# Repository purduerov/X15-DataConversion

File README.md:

# Readme for X15-DataConversion

Whenever you make a new part, download the datasheet and save it here _**and**_ with the part in the parts library

Always pull other people's changes before beginning to work
`git pull`

Be sure to push your changes after  working on them. Run:
1. `git add .` to add any files in this directory or a subdirectory
or `git add -u` to add any modified files
2. (Optional) `git clean -nX` to see what ignored files can be removed
	`git clean -fX` removes ignored files (Eagle backups)
3. `git commit -m "helpful commit message"` with a description of the work that you did
4. `git push` to push your work to github

Other helpful commands
* `git status` says information about modified and staged files
* `git log` shows the recent commits of the repository
* `git log filename.extension` show the recent commits for just that file
* `git checkout first-couple-letter-of-commit-id` lets you go back to a previous version
* `git checkout master` brings you back to the latest commit
* `git tag` lists the tags
* `git tag -a orderX -m "the version of the board placed for the X'th order"` tag a specific commit
* `git push --tags` needed to push tags to remote
* `git show orderX` show the commit log for the given tag
* `git checkout orderX` go back and interact with the files at the tagged commit

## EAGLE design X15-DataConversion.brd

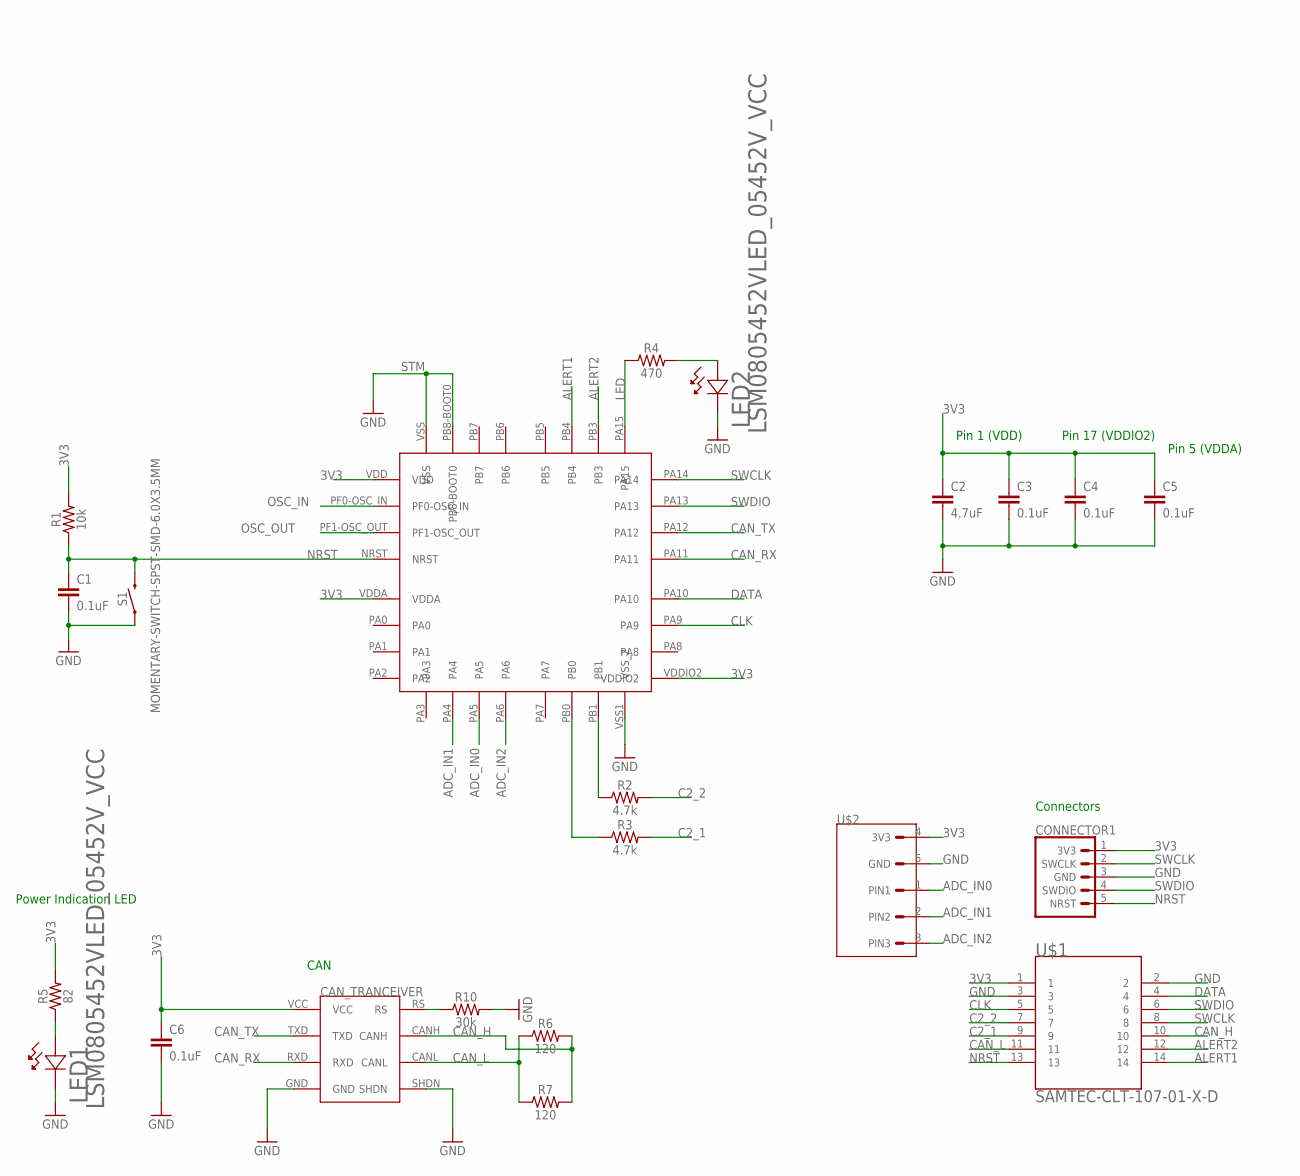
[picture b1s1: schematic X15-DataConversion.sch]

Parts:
C1, C3, C4, C5, C6: 0.1uF; 0603
C2: 4.7uF; 0603
CAN_TRANCEIVER: MAX3058ASA+
CONNECTOR1: 3V3 -SWCLK-GND-SWDIO- NRST; 1X05
LED1, LED2: LSM0805452VLED_05452V_VCC; LED_05452V_VCC
R1: 10k; 0603
R2, R3: 4.7k; 0603
R4: 470; 0603
R5: 82; 0603
R6, R7: 120; 0603
R10: 30k; 0603
S1: MOMENTARY-SWITCH-SPST-SMD-6.0X3.5MM; TACTILE_SWITCH_SMD_6.0X3.5MM
STM: STM32F042K6T6
U$1: BACKPLANE->DATACONV; SAMTEC-CLT-107-01-X-D-BACKPLANE
U$2: STM_CONN; 1X05

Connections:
3V3: C2.1, C3.1, C4.1, C5.1, C6.1, CAN_TRANCEIVER.VCC, CONNECTOR1.1 (3V3), R1.2, R5.2, STM.VDD, STM.VDDA, STM.VDDIO2, U$1.1, U$2.4 (3V3)
ADC_IN0: STM.PA5, U$2.1 (PIN1)
ADC_IN1: STM.PA4, U$2.2 (PIN2)
ADC_IN2: STM.PA6, U$2.3 (PIN3)
ALERT1: STM.PB4, U$1.14
ALERT2: STM.PB3, U$1.12
C2_1: R3.2, U$1.9
C2_2: R2.2, U$1.7
CAN_H: CAN_TRANCEIVER.CANH, R6.2, R7.2, U$1.10
CAN_L: CAN_TRANCEIVER.CANL, R6.1, R7.1, U$1.11
CAN_RX: CAN_TRANCEIVER.RXD, STM.PA11
CAN_TX: CAN_TRANCEIVER.TXD, STM.PA12
CLK: STM.PA9, U$1.5
DATA: STM.PA10, U$1.4
GND: C1.2, C2.2, C3.2, C4.2, C5.2, C6.2, CAN_TRANCEIVER.GND, CAN_TRANCEIVER.SHDN, CONNECTOR1.3 (GND), LED1.2, LED2.2, R10.2, S1.1, STM.PB8-BOOT0, STM.VSS, STM.VSS1 (VSS_2), U$1.2, U$1.3, U$2.5 (GND)
LED: R4.1, STM.PA15
unnamed: LED1.1, R5.1
unnamed: CAN_TRANCEIVER.RS, R10.1
unnamed: R2.1, STM.PB1
unnamed: R3.1, STM.PB0
unnamed: LED2.1, R4.2
NRST: C1.1, CONNECTOR1.5 (NRST), R1.1, S1.2, STM.NRST, U$1.13
OSC_IN: STM.PF0-OSC_IN
OSC_OUT: STM.PF1-OSC_OUT
SWCLK: CONNECTOR1.2 (SWCLK), STM.PA14, U$1.8
SWDIO: CONNECTOR1.4 (SWDIO), STM.PA13, U$1.6

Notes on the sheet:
Power Indication LED
Connectors
CAN
Pin 1 (VDD)
Pin 17 (VDDIO2)
Pin 5 (VDDA)

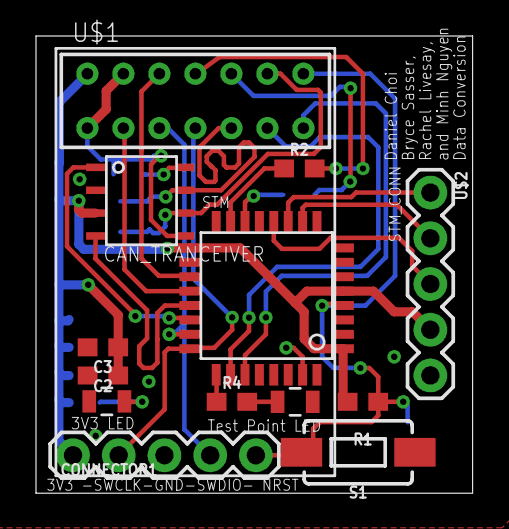
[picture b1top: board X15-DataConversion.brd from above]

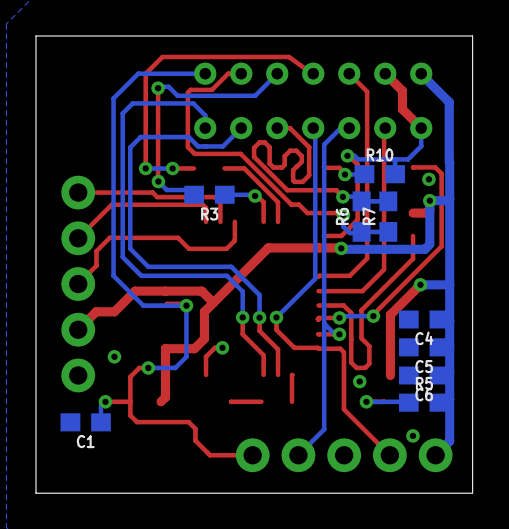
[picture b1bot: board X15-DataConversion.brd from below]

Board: 2 copper layers, 24.3 x 25.4 mm, 22 parts (9 on the bottom side), 24 nets.

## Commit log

2022-10-12 basic schematic finished
2022-10-15 schematic actually finished now
2022-10-15 added oscillator
2022-10-19 remove backup files
2022-10-19 board dimensions
2022-10-19 oscillator resistor and capacitor labels
2022-10-20 replaced oscillator with same one as on Pi Shield
2022-10-20 starting layout
2022-10-22 starting wiring
2022-10-26 Change to Parts Library (Replace Parts)
2022-10-26 working on layout
2022-10-27 started routing
2022-10-29 layout mostly done
2022-10-29 fixing board layout
2022-11-02 made can lines sameish length
2022-11-05 cleaning up board layout
2022-11-11 step file
2022-11-12 .gitignore file from last year + new step file
2022-11-19 alumni review changes
2022-11-19 fixed drc error
2022-12-01 removed oscillator and fixed trace widths
2022-12-03 added 5 pin connector
2022-12-03 fixed some trace lengths and widths and angles
2022-12-08 used the wrong connector so fixed that
2022-12-22 Fix label position
2023-04-08 testing

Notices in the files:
parts and their libraries:
SparkFun-Resistors: Licensing: Creative Commons ShareAlike 4.0 International - https://creativecommons.org/licenses/by-sa/4.0
COPYRIGHT: Copyright (C) 2022 Ultra Librarian. All rights reserved.
